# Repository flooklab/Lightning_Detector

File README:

Lightning Detector, an experimental open hardware project for early notification about approaching thunderstorm activity.
Copyright (C) 2024–2025 M. Frohne

Lightning Detector is licensed under the "CERN Open Hardware Licence, Version 2 - Weakly Reciprocal" or (at your option) any later version.
(please refer to the file 'LICENSE.OHL-W')

This does NOT apply to the firmware code that is found in the 'Firmware/' directory, which is instead
licensed under the "GNU General Public License, Version 3" or (at your option) any later version.
(please refer to the file 'LICENSE.GPL')

Note also that the firmware files in the directory 'Firmware/lightning_detector/fonts/' embed a subset of the Terminus Font
and are hence additionally licensed under the "SIL Open Font License, Version 1.1", with Reserved Font Name "Terminus Font".
(please refer to the file 'LICENSE.OFL')

###########################################################################################################################################

! ! ! ! ! WARNING ! ! ! ! !

Do NOT actually use Lightning Detector as a serious device to warn you about lightnings or thunderstorms!
It might be that lightnings will NOT be detected and that you will NOT be notified about present or
approaching thunderstorms. You have to assume that the device is inherently UNSAFE and does NOT
work properly. There is NO guarantee for the fitness for any particular purpose whatsoever.
UNDER NO CIRCUMSTANCES should you trust the information provided (or not provided) by the device.
Lightning Detector might NOT be tested thoroughly enough and is NOT even intended to be a reliable detector device.
Note that being in a thunderstorm (especially without sufficient protection around you (such as a building))
is a very dangerous situation as you might suddenly be struck by lightning, which is potentially LIFE-THREATENING.
Generally, you should always try to combine multiple sources of information to assess the current risk of thunderstorms
and lightning strikes. Check the weather forecast and watch the sky. Dark clouds can be an early indicator.
If in doubt (or when there is/are audible thunder or visible lightnings at the latest), please seek shelter!

! ! ! ! ! WARNING ! ! ! ! !

###########################################################################################################################################

For more information please see the file 'README.md'.

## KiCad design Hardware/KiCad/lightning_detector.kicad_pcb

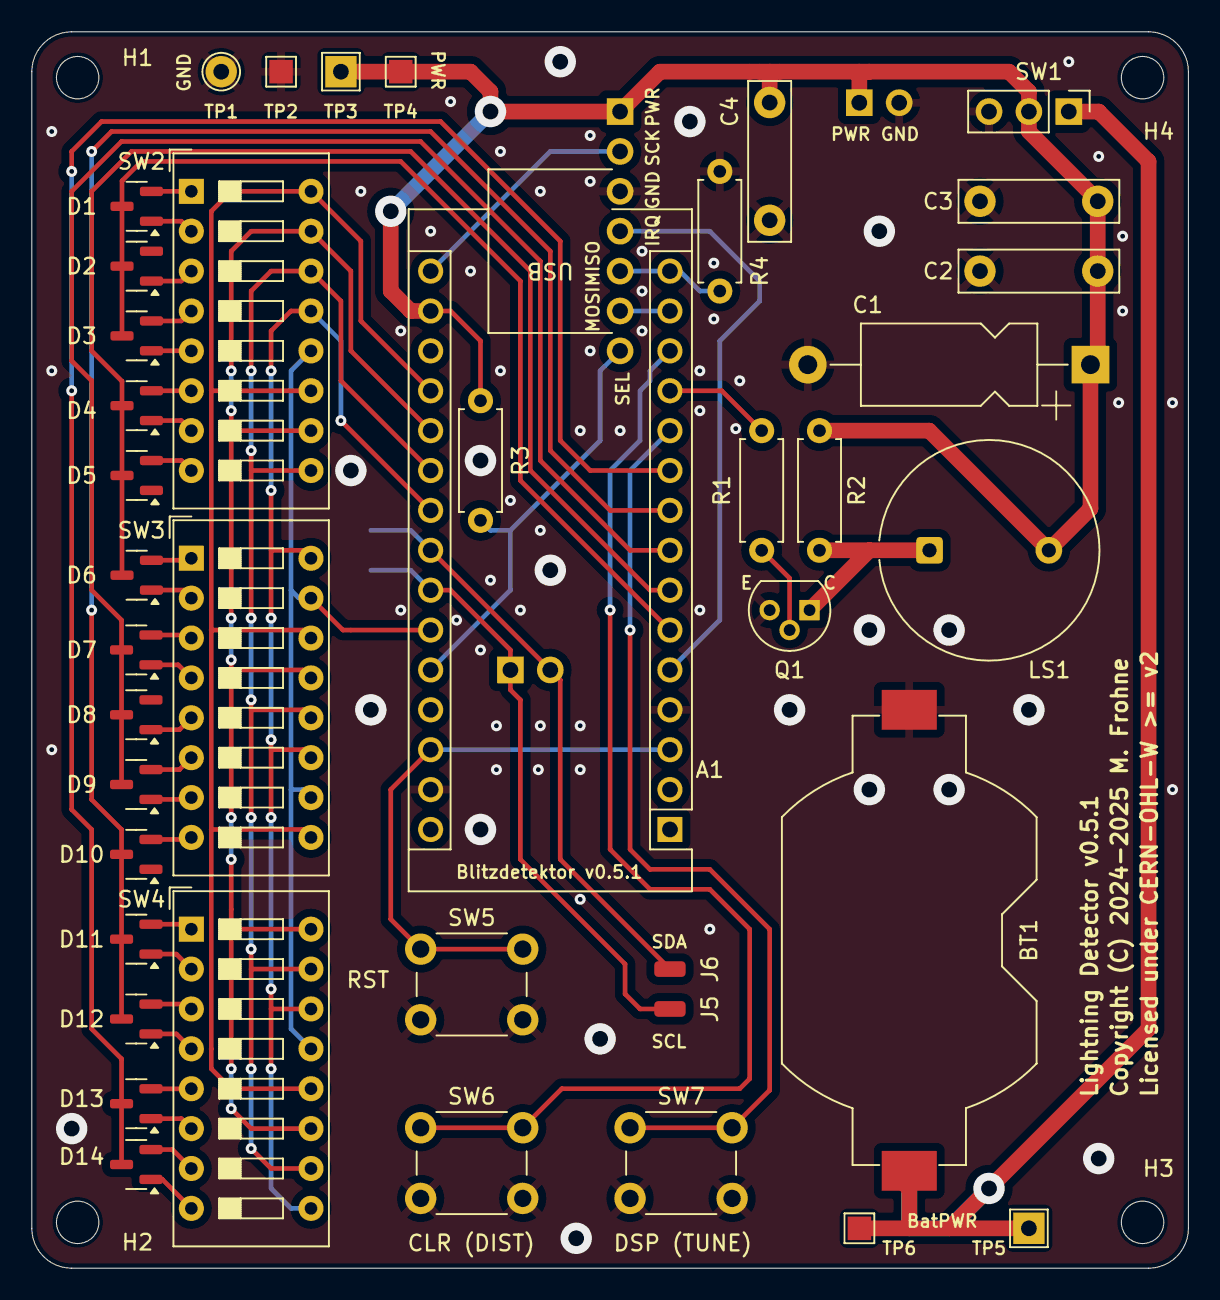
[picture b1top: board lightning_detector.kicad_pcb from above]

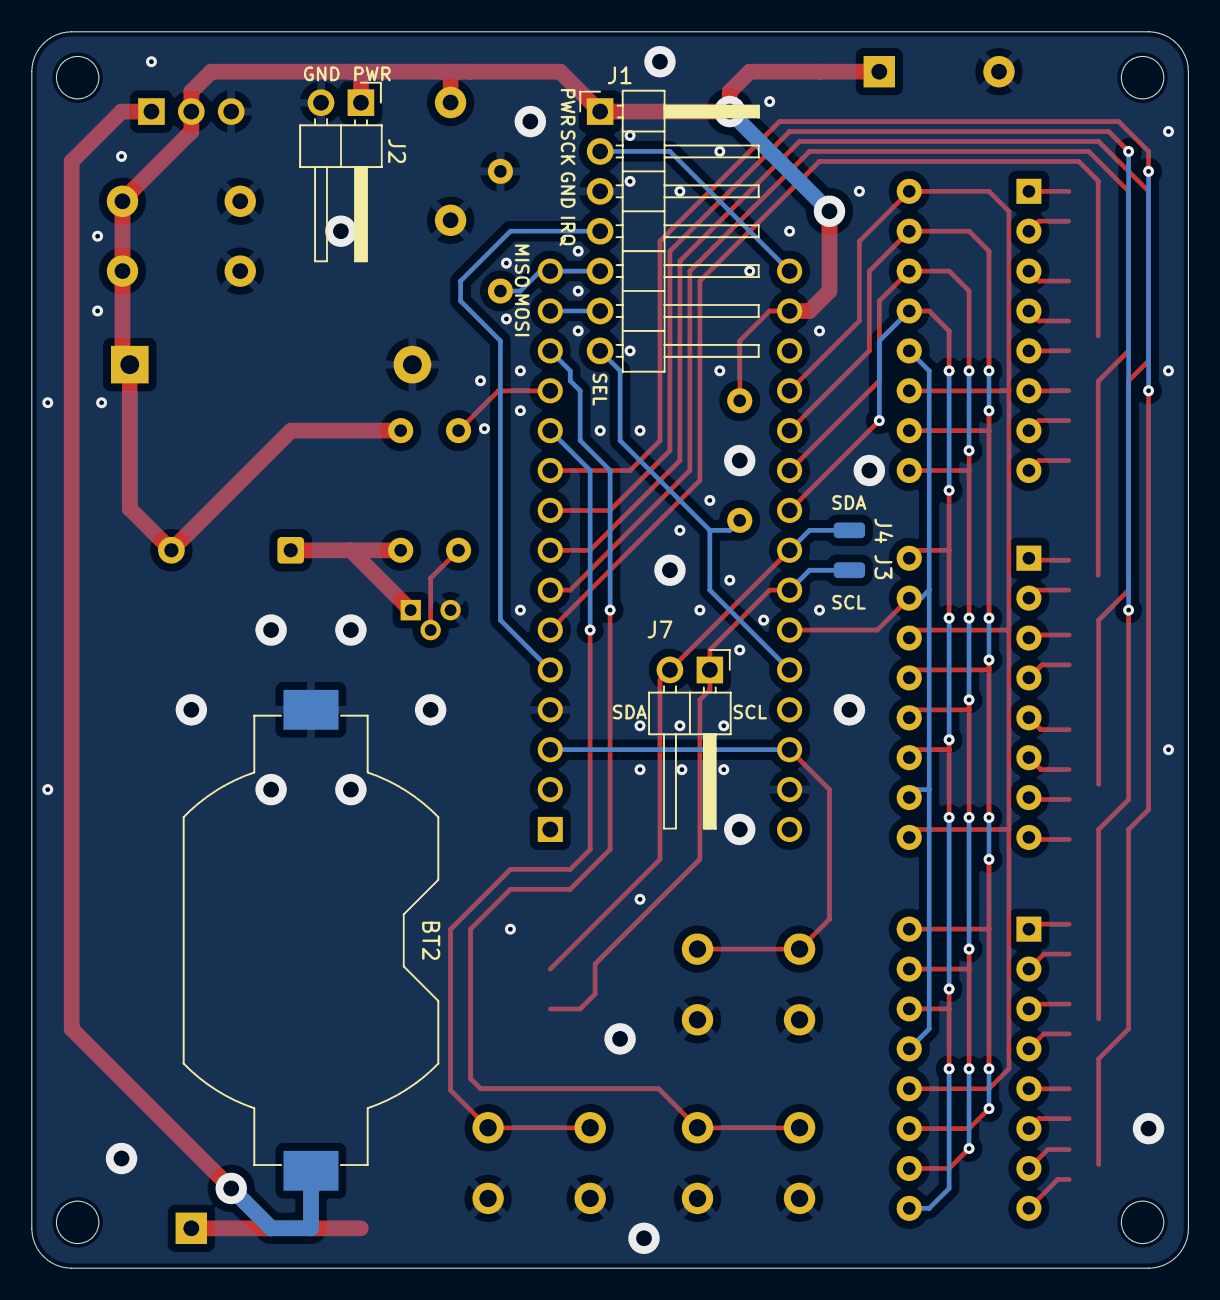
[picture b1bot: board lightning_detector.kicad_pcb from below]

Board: 2 copper layers, 73.7 x 78.7 mm, 51 parts (6 on the bottom side), 50 nets.

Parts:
A1: Arduino_Nano
BT1, BT2: BatteryHolder_Keystone_1058_1x2032
C1: CP_Axial_L11.0mm_D5.0mm_P18.00mm_Horizontal
C2, C3, C4: C_Rect_L10.0mm_W2.5mm_P7.50mm_MKS4
D1, D2, D3, D4, D5, D6, D7, D8, D9, D10, D11, D12, D13, D14: SOT-23
H1, H2, H3, H4: MountingHole_2.7mm_M2.5_DIN965
J1: PinHeader_1x07_P2.54mm_Horizontal
J2, J7: PinHeader_1x02_P2.54mm_Horizontal
J3, J4, J5, J6: SolderWirePad_1x01_SMD_1x2mm
LS1: Indicator_PUI_AI-1440-TWT-24V-2-R
Q1: TO-92
R1, R2, R3, R4: R_Axial_DIN0207_L6.3mm_D2.5mm_P7.62mm_Horizontal
SW1: PinHeader_1x03_P2.54mm_Vertical
SW2, SW3, SW4: SW_DIP_SPSTx08_Slide_9.78x22.5mm_W7.62mm_P2.54mm
SW5, SW6, SW7: SW_PUSH_6mm
TP1: TestPoint_THTPad_D2.0mm_Drill1.0mm
TP2, TP4, TP6: TestPoint_Pad_1.5x1.5mm
TP3, TP5: TestPoint_THTPad_2.0x2.0mm_Drill1.0mm

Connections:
ARDUINO-RESET: A1.3, A1.28, SW5.1
AS3935-IRQ: A1.5, J1.4
BatPower: BT1.1, BT2.1, SW1.1, TP5.1, TP6.1
Beeper: LS1.1, Q1.1, R2.2
Beeper-CTRL: A1.12, R1.1
Beeper-TrBase: Q1.2, R1.2
ClearStatsBut: A1.13, SW6.1
DIP-Sel-1: A1.6, D1.3, D2.3, D3.3
DIP-Sel-1-P1: D1.2, SW2.1
DIP-Sel-1-P2: D1.1, SW2.2
DIP-Sel-1-P3: D2.1, SW2.3
DIP-Sel-1-P4: D3.2, SW2.4
DIP-Sel-1-P5: D3.1, SW2.5
DIP-Sel-2: A1.7, D4.3, D5.3, D6.3
DIP-Sel-2-P1: D4.2, SW2.6
DIP-Sel-2-P2: D4.1, SW2.7
DIP-Sel-2-P3: D5.2, SW2.8
DIP-Sel-2-P4: D6.2, SW3.1
DIP-Sel-2-P5: D6.1, SW3.2
DIP-Sel-3: A1.8, D7.3, D8.3, D9.3
DIP-Sel-3-P1: D7.2, SW3.3
DIP-Sel-3-P2: D7.1, SW3.4
DIP-Sel-3-P3: D8.1, SW3.5
DIP-Sel-3-P4: D9.2, SW3.6
DIP-Sel-3-P5: D9.1, SW3.7
DIP-Sel-4: A1.9, D10.3, D11.3, D12.3
DIP-Sel-4-P1: D10.2, SW3.8
DIP-Sel-4-P2: D11.2, SW4.1
DIP-Sel-4-P3: D11.1, SW4.2
DIP-Sel-4-P4: D12.2, SW4.3
DIP-Sel-4-P5: D12.1, SW4.4
DIP-Sel-5: A1.10, D13.3, D14.3
DIP-Sel-5-P1: D13.2, SW4.5
DIP-Sel-5-P2: D13.1, SW4.6
DIP-Sel-5-P3: D14.2, SW4.7
DIP-Sel-5-P4: D14.1, SW4.8
DIP-Sens-1: A1.19, SW2.11, SW2.16, SW3.9, SW3.14, SW4.12
DIP-Sens-2: A1.20, SW2.10, SW2.15, SW3.13, SW4.11, SW4.16
DIP-Sens-3: A1.21, SW2.9, SW2.14, SW3.12, SW4.10, SW4.15
DIP-Sens-4: A1.22, SW2.13, SW3.11, SW3.16, SW4.9, SW4.14
DIP-Sens-5: A1.25, SW2.12, SW3.10, SW3.15, SW4.13
DisplayBut: A1.11, SW7.1
GND: A1.4, A1.29, BT1.2, BT2.2, C1.2, C2.1, C3.1, C4.1, J1.3, J2.2, Q1.3, R4.2, SW1.3, SW5.2, SW6.2, SW7.2, TP1.1, TP2.1
I2C-SCL: A1.24, J3.1, J5.1, J7.1
I2C-SDA: A1.23, J4.1, J6.1, J7.2
Power: A1.17, C1.1, C2.2, C3.2, C4.2, J1.1, J2.1, LS1.2, R2.1, R3.2, SW1.2, TP3.1, TP4.1
SPI-CLK: A1.16, J1.2
SPI-MISO: A1.15, J1.5, R4.1
SPI-MOSI: A1.14, J1.6
SPISel-AS3935: A1.26, J1.7, R3.1

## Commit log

2024-04-07 Initial commit.
    Add Lightning Detector 0.5.0.
2025-01-01 Add example STEP and STL files for a 3D printed case.
2025-01-01 Use smaller lightning rate threshold for switching to smaller VDD measurement interval.
2025-01-01 Update design files to KiCad version 8 and fix footprint overlap.
2025-01-01 Update Gerber files.
2025-01-01 Update schematics.
2025-01-01 Update render images.
2025-01-01 Add pictures of 3D printed case assembly.
2025-01-01 Update version number.
2025-01-01 Clarify README.md.
2025-01-02 Update copyright years.

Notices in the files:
Hardware/KiCad/lightning_detector.kicad_pcb:
Licensed under CERN-OHL-W >= v2
Licensed under CERN-OHL-W version 2, or (at your option) any later version
